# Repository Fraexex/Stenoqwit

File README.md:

# Stenoqwit

## Project Owner

**Name:** Christian Galvez
**Virginia Tech Email:** chant4@vt.edu

## Project Overview

Complete circuit creation using a stenograph-like keyboard. This includes component placement, routing, user-defined symbols, and export to KiCad (no mouse or code required for the user).

## What I Hope to Learn

QMK firmware and ergonomic design is my current main focus. After I've settled on a good ergonomic design, I hope to learn more on challenges EDA tools like KiCAD are facing.

## Design and Implementation

Refer to `project_proposal_v3.pptx`

## Bill of Materials

Refer to files in `bom/`

## Timeline and Milestones

| Milestone | Target Date | Status |
|---|---|---|
| KiCAD First PCB Design | 9/11 | 100% |

## Progress Log

September 11, 2001, commemoration date

### 2026-09-11

Never forget

## Project Files

```
Stenoqwit/
├── bom/
│   ├── CPL.csv
│   ├── DigiKeyBOM.xlsx
│   └── JLCBOM.csv
├── doc/
│   └── # TODO
├── firmware/qmk/keyboards/stenoqwit/
│   ├── config.h
│   ├── keymap.c
│   └── rules.mk
├── gerber/
│   ├── stenoqwit-B_Cu.gbr
│   ├── stenoqwit-B_Mask.gbr
│   ├── stenoqwit-B_Paste.gbr
│   ├── stenoqwit-Edge_Cuts.gbr
│   ├── stenoqwit-F_Cu.gbr
│   ├── stenoqwit-F_Mask.gbr
│   ├── stenoqwit-F_Paste.gbr
│   ├── stenoqwit-F_Silkscreen.gbr
│   ├── stenoqwit-job.gbrjob
│   ├── stenoqwit-NPTH.drl
│   └── stenoqwit-PTH.drl
├── hero.png
├── project_proposal_v3.pptx
├── README.md
├── stenoqwit.kicad_pcb
├── stenoqwit.kicad_prl
├── stenoqwit.kicad_pro
└── stenoqwit.kicad_sch
```

## Useful Links

Refer to files in `doc/`

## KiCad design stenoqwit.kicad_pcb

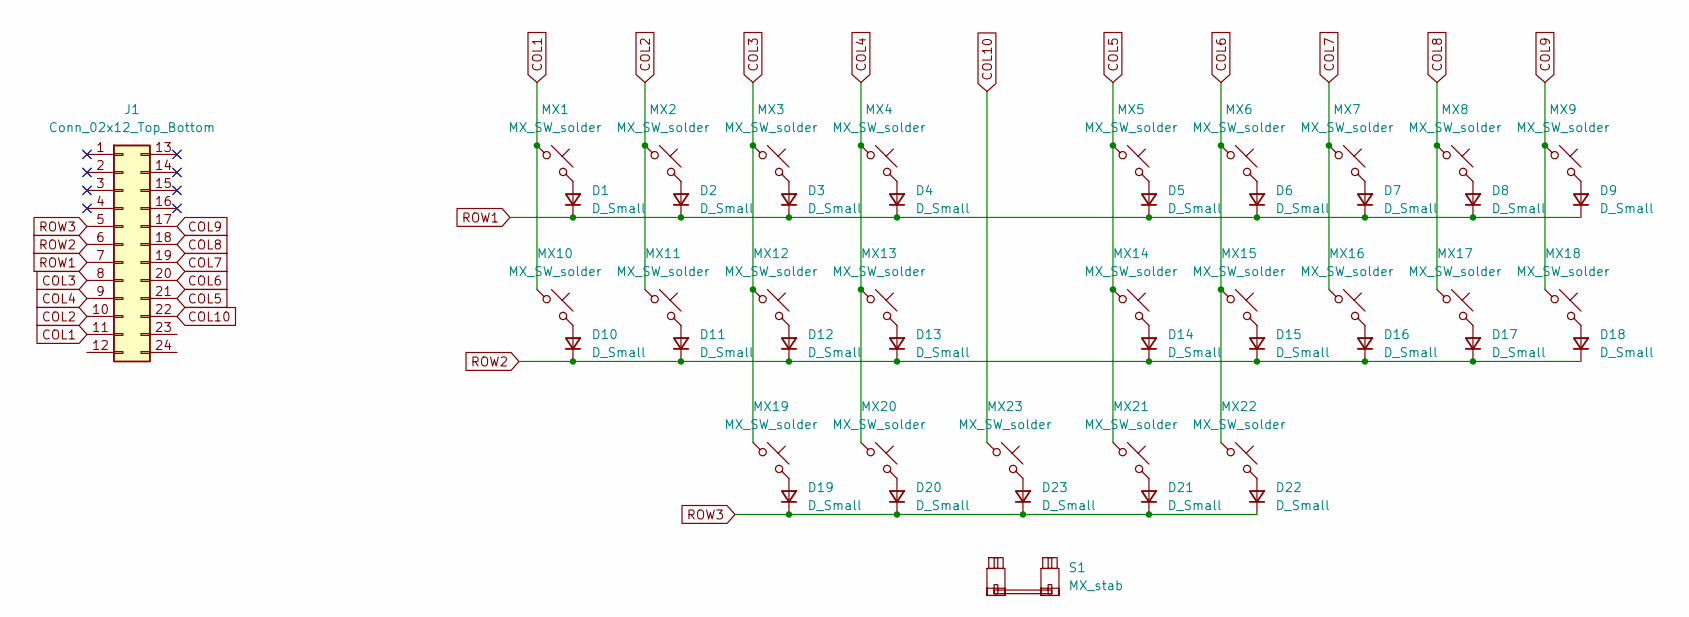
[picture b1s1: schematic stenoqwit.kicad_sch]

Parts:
D1, D2, D3, D4, D5, D6, D7, D8, D9, D10, D11, D12, D13, D14, D15, D16, D17, D18, D19, D20, D21, D22, D23: D_Small; D_SOD-123
J1: Conn_02x12_Top_Bottom; ProMicro_USBup
MX1, MX2, MX3, MX4, MX5, MX6, MX7, MX8, MX9, MX10, MX11, MX12, MX13, MX14, MX15, MX16, MX17, MX18, MX19, MX20, MX21, MX22, MX23: MX_SW_solder; SW_MX_1u
S1: MX_stab; STAB_MX_P_2u

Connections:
COL1: J1.11, MX1.1, MX10.1
COL2: J1.10, MX2.1, MX11.1
COL3: J1.8, MX3.1, MX12.1, MX19.1
COL4: J1.9, MX4.1, MX13.1, MX20.1
COL5: J1.21, MX5.1, MX14.1, MX21.1
COL6: J1.20, MX6.1, MX15.1, MX22.1
COL7: J1.19, MX7.1, MX16.1
COL8: J1.18, MX8.1, MX17.1
COL9: J1.17, MX9.1, MX18.1
COL10: J1.22, MX23.1
unnamed: D1.2 (A), MX1.2
unnamed: D2.2 (A), MX2.2
unnamed: D3.2 (A), MX3.2
unnamed: D4.2 (A), MX4.2
unnamed: D5.2 (A), MX5.2
unnamed: D6.2 (A), MX6.2
unnamed: D7.2 (A), MX7.2
unnamed: D8.2 (A), MX8.2
unnamed: D9.2 (A), MX9.2
unnamed: D10.2 (A), MX10.2
unnamed: D11.2 (A), MX11.2
unnamed: D12.2 (A), MX12.2
unnamed: D13.2 (A), MX13.2
unnamed: D14.2 (A), MX14.2
unnamed: D15.2 (A), MX15.2
unnamed: D16.2 (A), MX16.2
unnamed: D17.2 (A), MX17.2
unnamed: D18.2 (A), MX18.2
unnamed: D19.2 (A), MX19.2
unnamed: D20.2 (A), MX20.2
unnamed: D21.2 (A), MX21.2
unnamed: D22.2 (A), MX22.2
unnamed: D23.2 (A), MX23.2
ROW1: D1.1 (K), D2.1 (K), D3.1 (K), D4.1 (K), D5.1 (K), D6.1 (K), D7.1 (K), D8.1 (K), D9.1 (K), J1.7
ROW2: D10.1 (K), D11.1 (K), D12.1 (K), D13.1 (K), D14.1 (K), D15.1 (K), D16.1 (K), D17.1 (K), D18.1 (K), J1.6
ROW3: D19.1 (K), D20.1 (K), D21.1 (K), D22.1 (K), D23.1 (K), J1.5

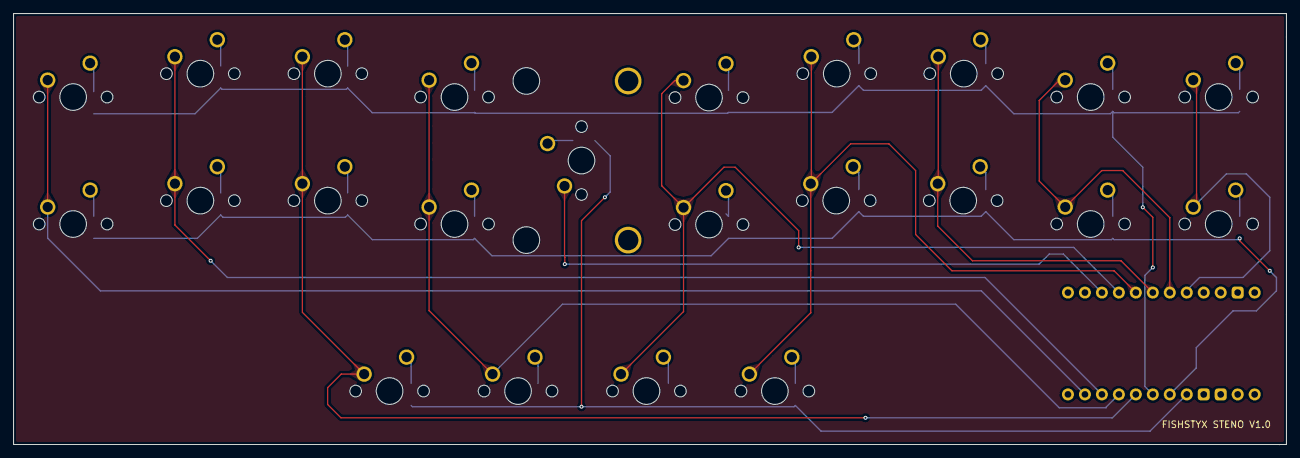
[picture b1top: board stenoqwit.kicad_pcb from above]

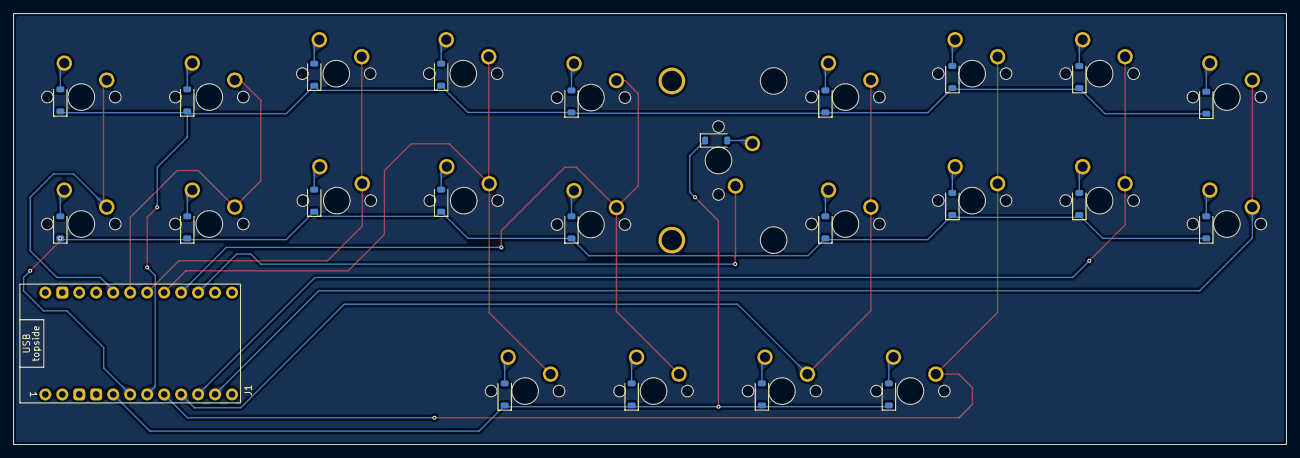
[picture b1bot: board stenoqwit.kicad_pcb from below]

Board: 2 copper layers, 190.5 x 64.5 mm, 48 parts (24 on the bottom side), 36 nets.

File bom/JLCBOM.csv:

Comment,Designator,Footprint,JLCPCB Part #（optional）
D_Small,"D1, D2, D3, D4, D5, D6, D7, D8, D9, D10, D11, D12, D13, D14, D15, D16, D17, D18, D19, D20, D21, D22, D23",D_SOD-123,
Conn_02x12_Top_Bottom,J1,ProMicro_USBup,
MX_SW_solder,"MX1, MX2, MX3, MX4, MX5, MX6, MX7, MX8, MX9, MX10, MX11, MX12, MX13, MX14, MX15, MX16, MX17, MX18, MX19, MX20, MX21, MX22, MX23",SW_MX_1u,
MX_stab,S1,STAB_MX_P_2u,
